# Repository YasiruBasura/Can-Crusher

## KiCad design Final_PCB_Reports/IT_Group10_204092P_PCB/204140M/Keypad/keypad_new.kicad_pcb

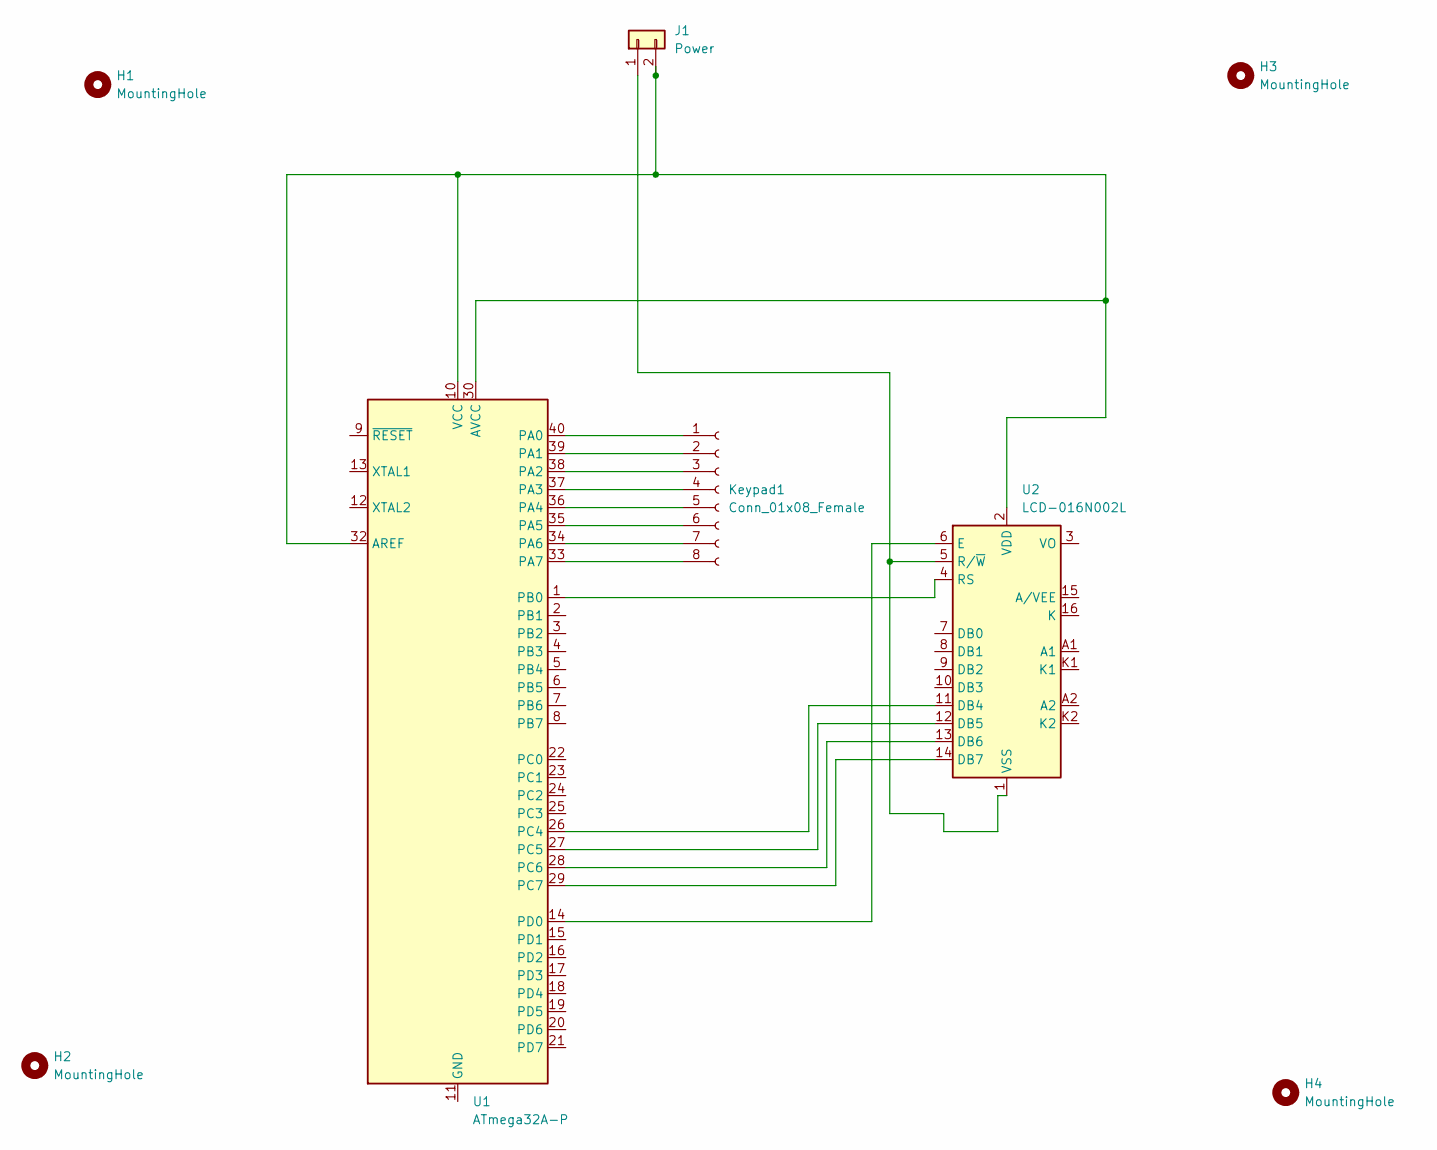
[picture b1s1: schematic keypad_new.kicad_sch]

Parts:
H1, H2, H3, H4: MountingHole; MountingHole_3.5mm_Pad
J1: Power; PinHeader_1x02_P2.54mm_Horizontal
Keypad1: Conn_01x08_Female; PinSocket_1x08_P1.27mm_Vertical
U1: ATmega32A-P; DIP-40_W15.24mm
U2: LCD-016N002L

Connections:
unnamed: Keypad1.1, U1.40 (PA0)
unnamed: Keypad1.2, U1.39 (PA1)
unnamed: Keypad1.3, U1.38 (PA2)
unnamed: Keypad1.4, U1.37 (PA3)
unnamed: Keypad1.5, U1.36 (PA4)
unnamed: Keypad1.6, U1.35 (PA5)
unnamed: Keypad1.7, U1.34 (PA6)
unnamed: Keypad1.8, U1.33 (PA7)
unnamed: U1.1 (PB0), U2.4 (RS)
unnamed: U1.11 (GND), U1.31 (GND)
unnamed: U1.14 (PD0), U2.6 (E)
unnamed: U1.26 (PC4), U2.11 (DB4)
unnamed: U1.27 (PC5), U2.12 (DB5)
unnamed: U1.28 (PC6), U2.13 (DB6)
unnamed: U1.29 (PC7), U2.14 (DB7)
unnamed: J1.2, U1.10 (VCC), U1.30 (AVCC), U1.32 (AREF), U2.2 (VDD)
unnamed: J1.1, U2.1 (VSS), U2.5 (R/~W)

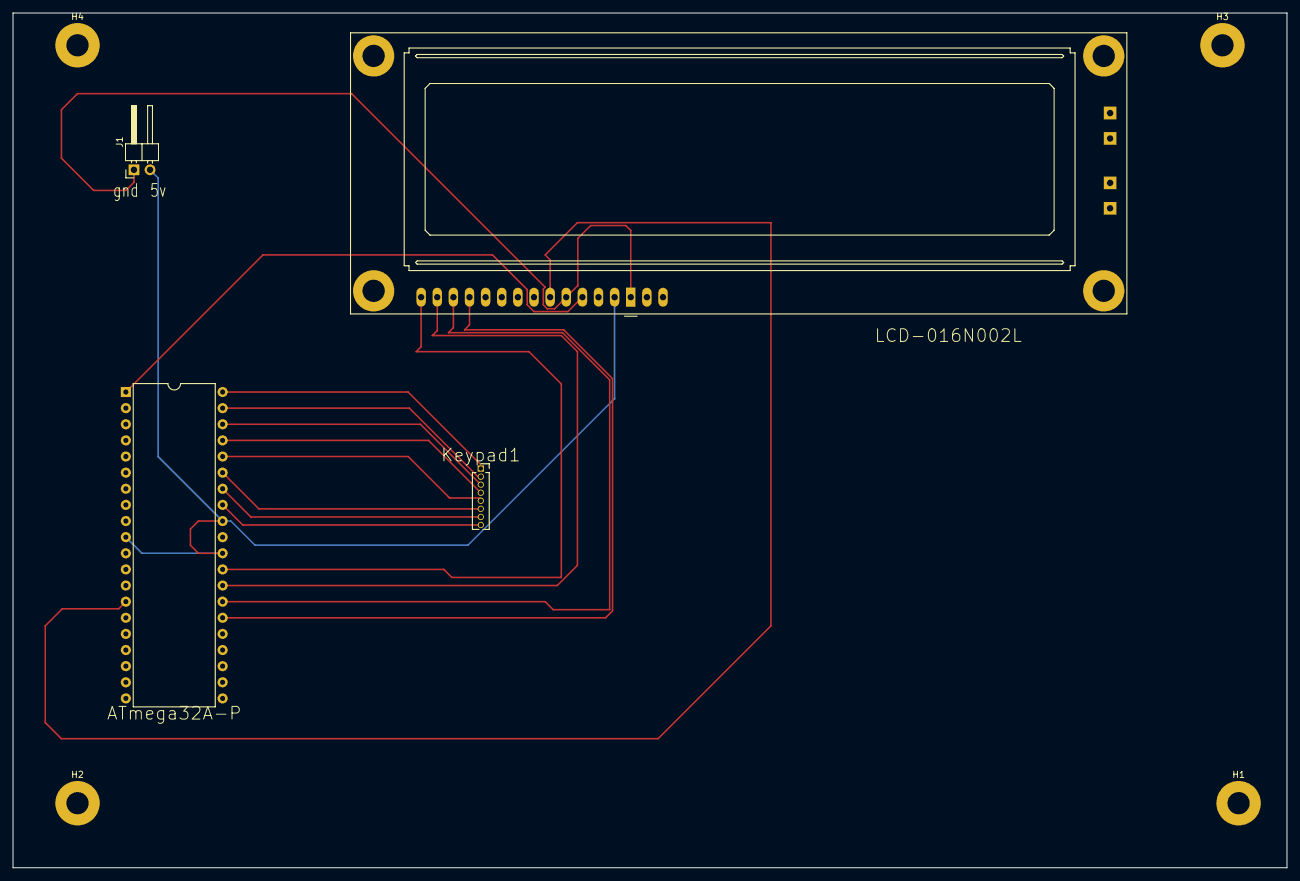
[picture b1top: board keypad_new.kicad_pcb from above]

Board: 2 copper layers, 200.7 x 134.6 mm, 8 parts (0 on the bottom side), 17 nets.

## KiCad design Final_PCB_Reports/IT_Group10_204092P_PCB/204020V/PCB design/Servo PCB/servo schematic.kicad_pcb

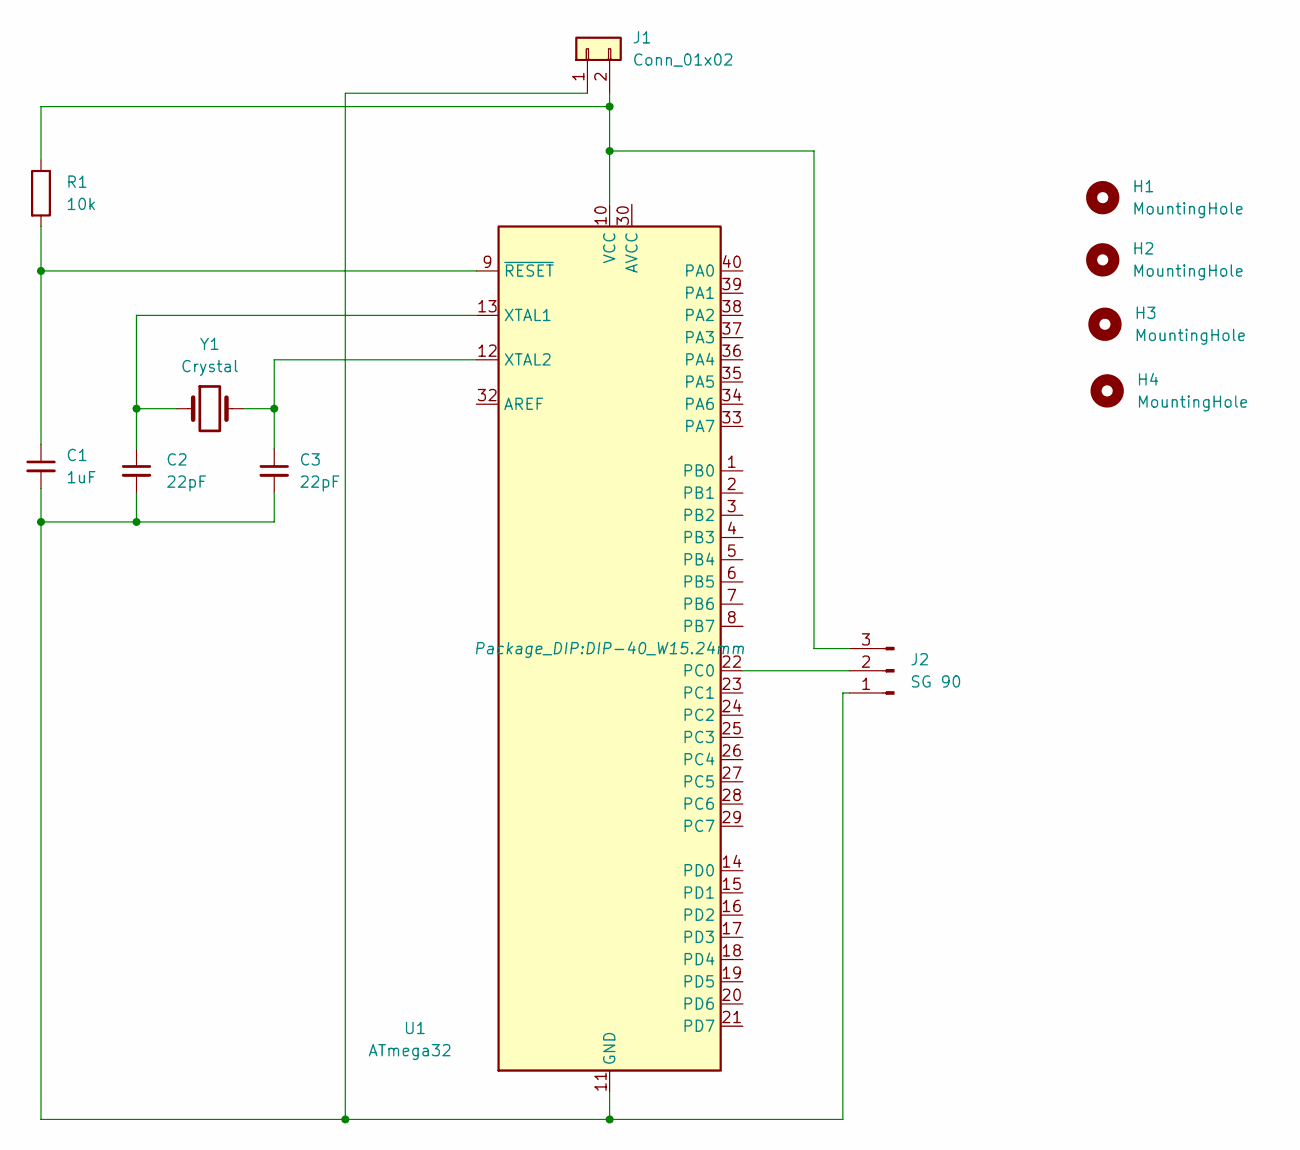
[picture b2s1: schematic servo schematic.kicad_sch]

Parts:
C1: 1uF; CP_Radial_D4.0mm_P1.50mm
C2, C3: 22pF; CP_Radial_D4.0mm_P1.50mm
H1, H2, H3, H4: MountingHole; MountingHole_3.5mm_Pad
J1: Conn_01x02; PinHeader_1x02_P2.54mm_Horizontal
J2: SG 90; PinSocket_1x03_P1.27mm_Vertical
R1: 10k; R_Axial_DIN0204_L3.6mm_D1.6mm_P5.08mm_Horizontal
U1: ATmega32; DIP-40_W15.24mm
Y1: Crystal; Crystal_AT310_D3.0mm_L10.0mm_Vertical

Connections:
unnamed: C1.1, R1.2, U1.9 (~RESET)
unnamed: C1.2, C2.2, C3.2, J1.1, J2.1, U1.11 (GND), U1.31 (GND)
unnamed: C2.1, U1.13 (XTAL1), Y1.1
unnamed: C3.1, U1.12 (XTAL2), Y1.2
unnamed: J1.2, J2.3, R1.1, U1.10 (VCC)
unnamed: J2.2, U1.22 (PC0)

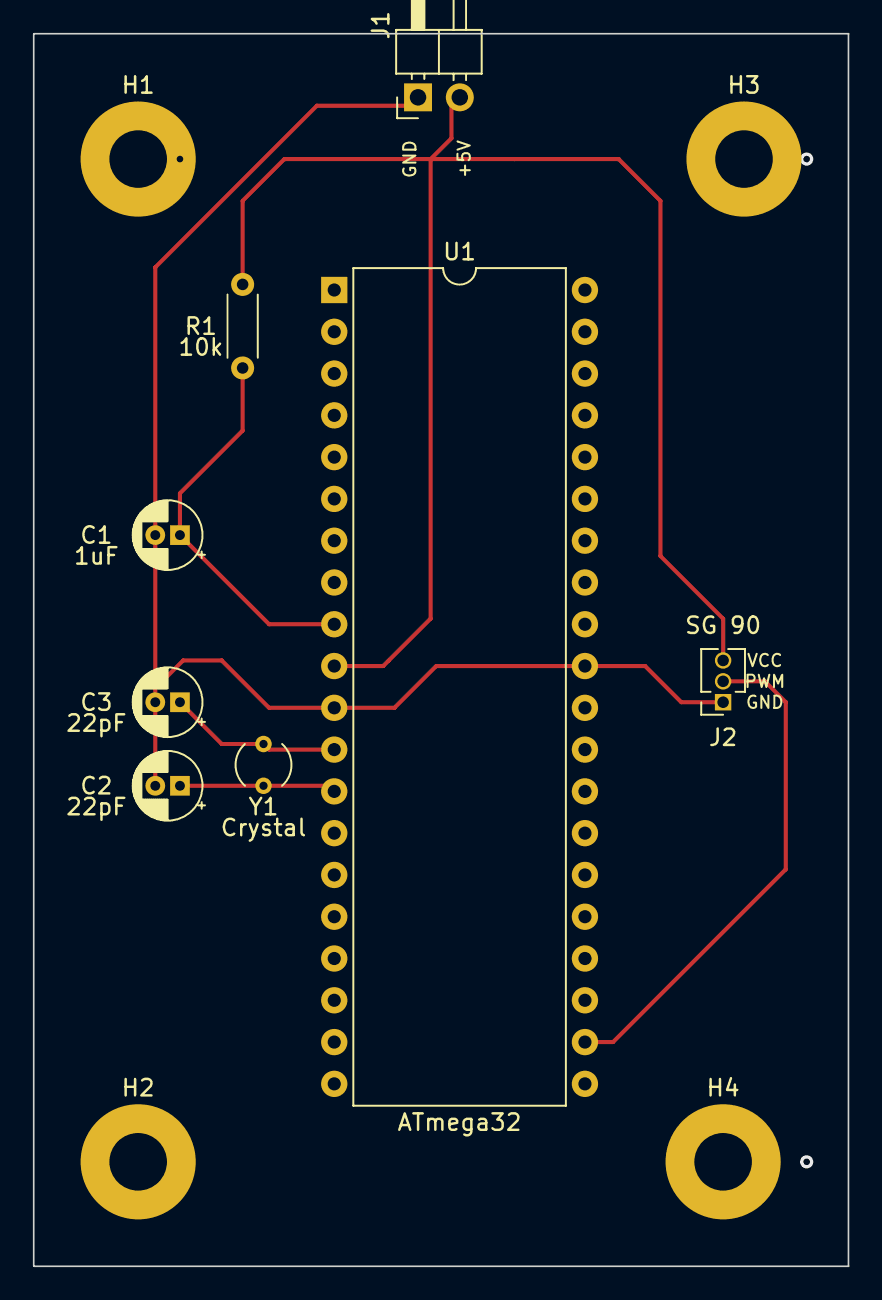
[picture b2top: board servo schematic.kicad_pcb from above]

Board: 2 copper layers, 49.5 x 74.9 mm, 12 parts (0 on the bottom side), 6 nets.

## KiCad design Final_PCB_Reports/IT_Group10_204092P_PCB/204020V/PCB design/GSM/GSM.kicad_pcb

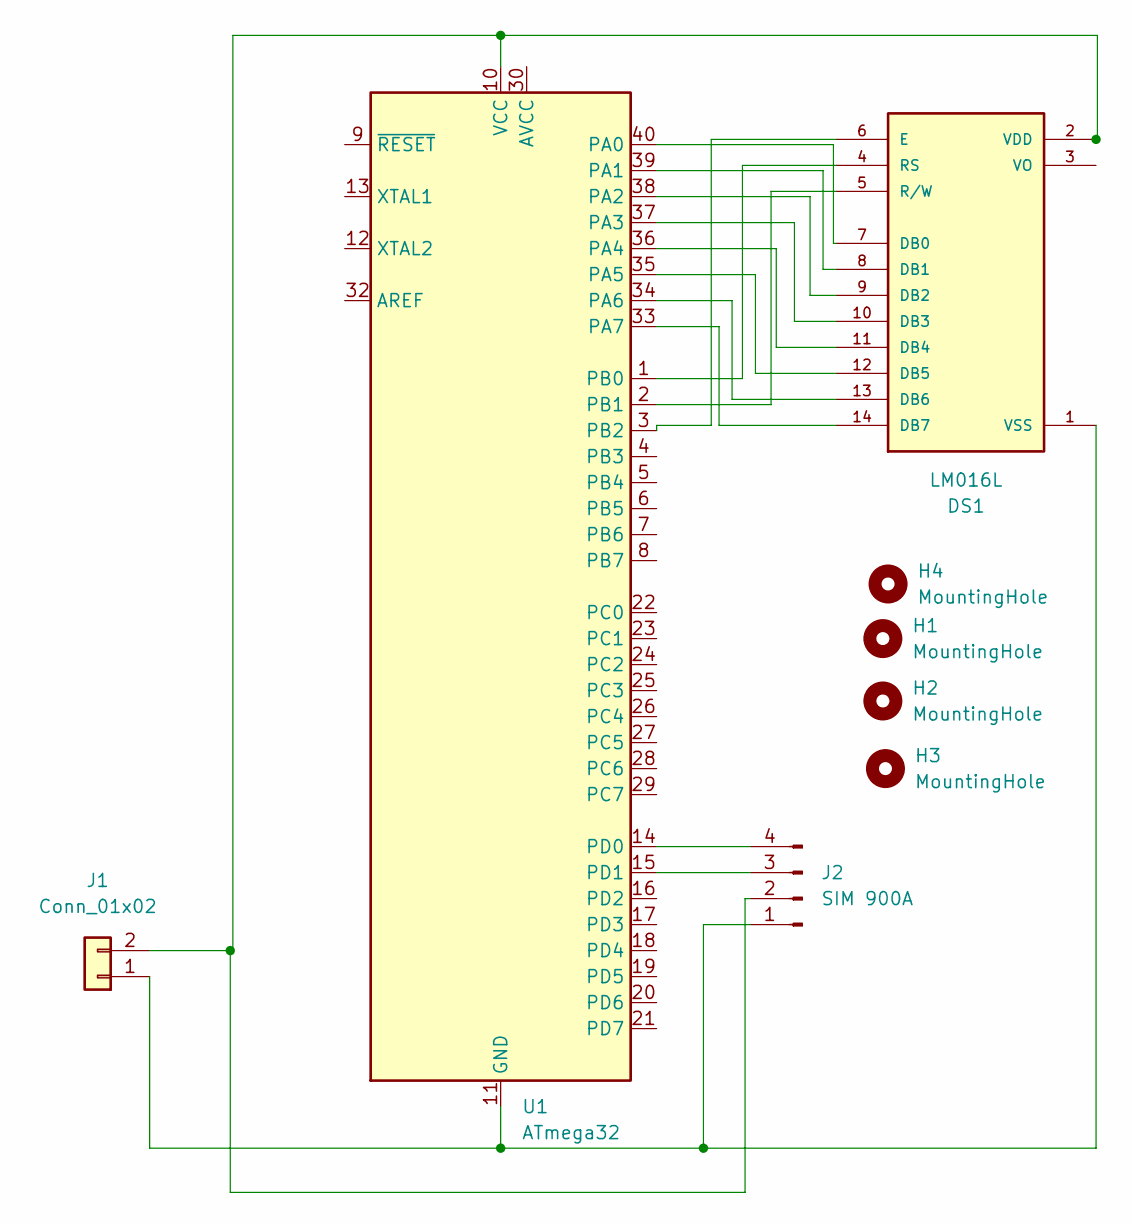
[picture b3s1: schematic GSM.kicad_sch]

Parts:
DS1: LM016L; LCD_LM016L
H1, H2, H3, H4: MountingHole; MountingHole_3.5mm_Pad
J1: Conn_01x02; PinHeader_1x02_P2.54mm_Horizontal
J2: SIM 900A; PinSocket_1x04_P1.27mm_Vertical
U1: ATmega32; DIP-40_W15.24mm

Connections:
unnamed: DS1.4 (RS), U1.1 (PB0)
unnamed: DS1.5 (R/W), U1.2 (PB1)
unnamed: DS1.6 (E), U1.3 (PB2)
unnamed: DS1.7 (DB0), U1.40 (PA0)
unnamed: DS1.8 (DB1), U1.39 (PA1)
unnamed: DS1.9 (DB2), U1.38 (PA2)
unnamed: DS1.10 (DB3), U1.37 (PA3)
unnamed: DS1.11 (DB4), U1.36 (PA4)
unnamed: DS1.12 (DB5), U1.35 (PA5)
unnamed: DS1.13 (DB6), U1.34 (PA6)
unnamed: DS1.14 (DB7), U1.33 (PA7)
unnamed: DS1.1 (VSS), J1.1, J2.1, U1.11 (GND), U1.31 (GND)
unnamed: DS1.2 (VDD), J1.2, J2.2, U1.10 (VCC)
unnamed: J2.3, U1.15 (PD1)
unnamed: J2.4, U1.14 (PD0)

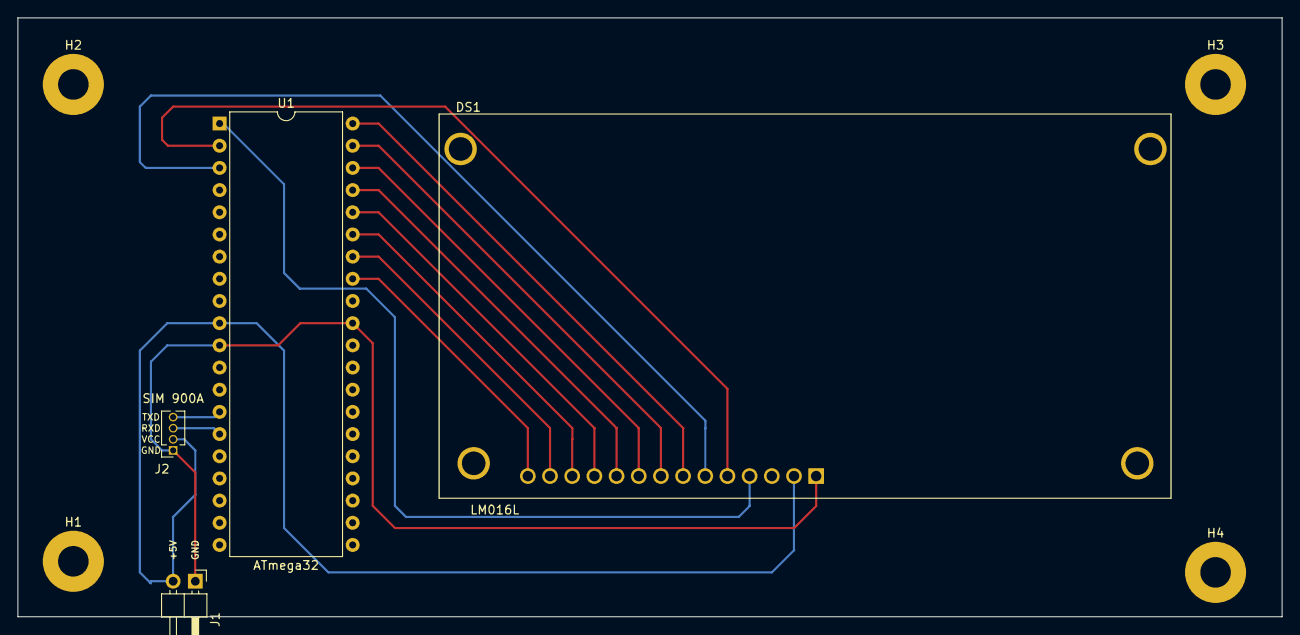
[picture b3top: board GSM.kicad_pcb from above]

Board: 2 copper layers, 144.8 x 68.6 mm, 8 parts (0 on the bottom side), 15 nets.

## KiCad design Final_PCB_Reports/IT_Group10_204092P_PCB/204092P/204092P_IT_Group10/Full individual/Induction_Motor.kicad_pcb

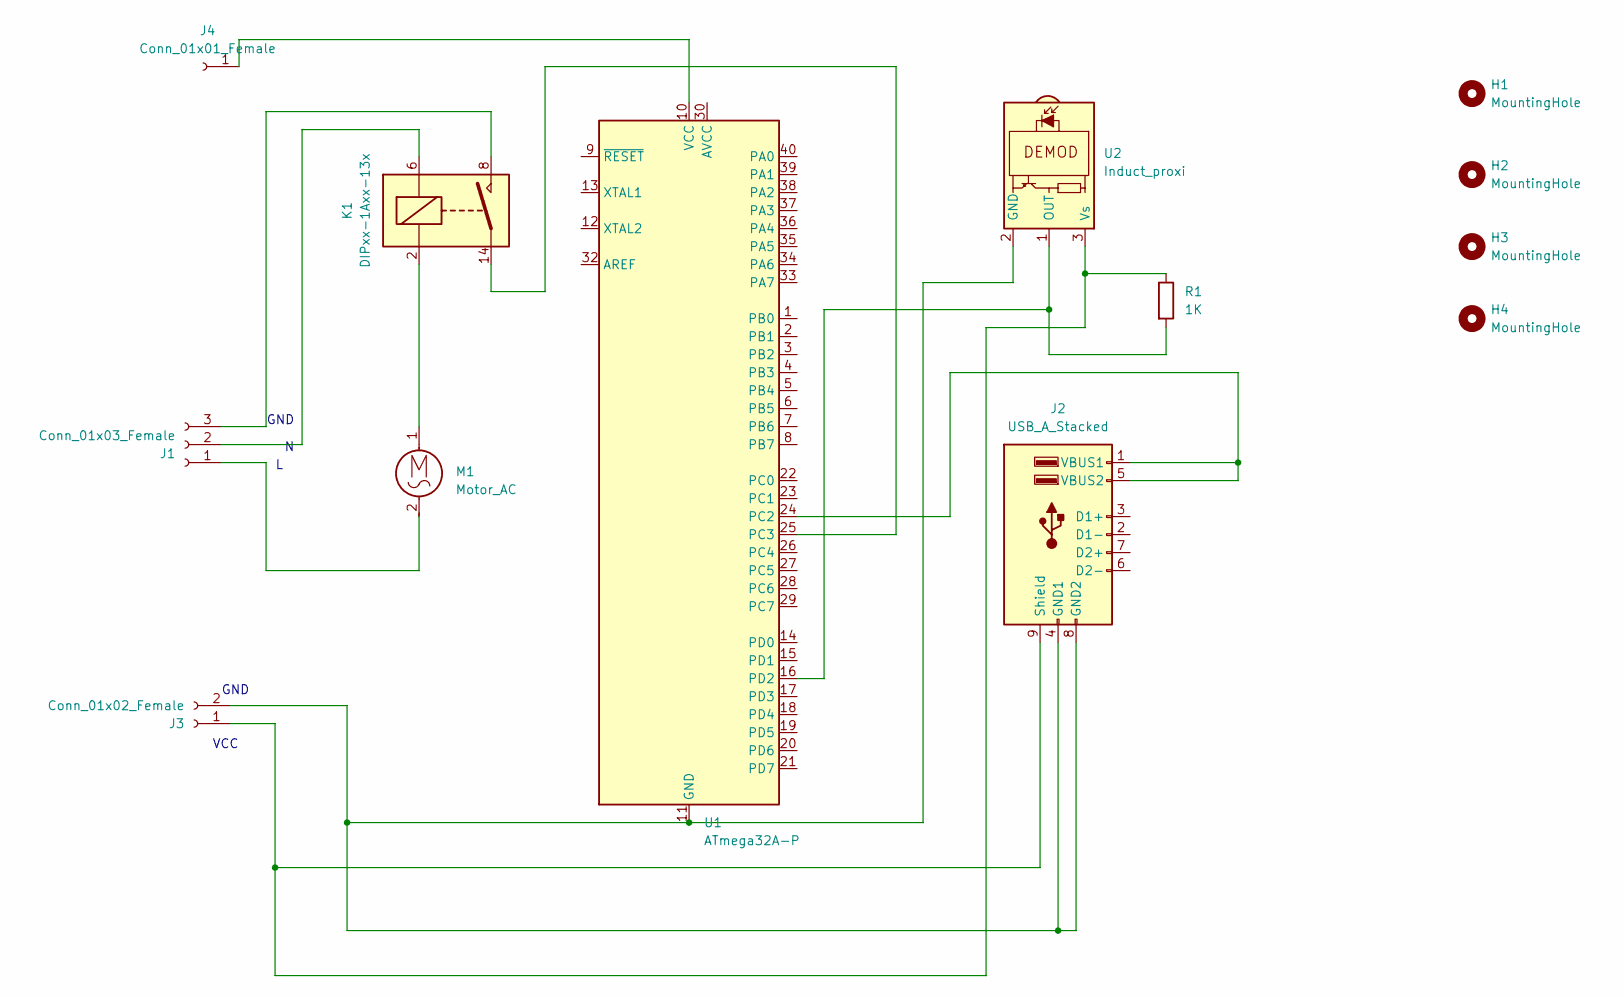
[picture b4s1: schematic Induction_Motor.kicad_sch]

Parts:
H1, H2, H3, H4: MountingHole; MountingHole_3.5mm_Pad
J1: Conn_01x03_Female; PinSocket_1x03_P2.54mm_Vertical
J2: USB_A_Stacked; USB_A_Wuerth_61400826021_Horizontal_Stacked
J3: Conn_01x02_Female; PinSocket_1x02_P2.54mm_Vertical
J4: Conn_01x01_Female; PinSocket_1x01_P2.54mm_Vertical
K1: DIPxx-1Axx-13x; Relay_StandexMeder_DIP_LowProfile
M1: Motor_AC; PinSocket_1x02_P2.54mm_Vertical
R1: 1K; R_Axial_DIN0204_L3.6mm_D1.6mm_P5.08mm_Horizontal
U1: ATmega32A-P; DIP-40_W15.24mm
U2: Induct_proxi; Vishay_MINICAST-3Pin

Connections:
unnamed: J1.1, M1.2
unnamed: J1.2, K1.6
unnamed: J1.3, K1.8
unnamed: J2.1 (VBUS1), J2.5 (VBUS2), U1.24 (PC2)
unnamed: J2.4 (GND1), J2.8 (GND2), J3.2, U1.11 (GND), U1.31 (GND), U2.2 (GND)
unnamed: J2.9 (Shield), J3.1, R1.1, U2.3 (Vs)
unnamed: K1.2, M1.1
unnamed: K1.14, U1.25 (PC3)
unnamed: J4.1, U1.10 (VCC)
unnamed: R1.2, U1.16 (PD2), U2.1 (OUT)

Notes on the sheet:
GND
VCC

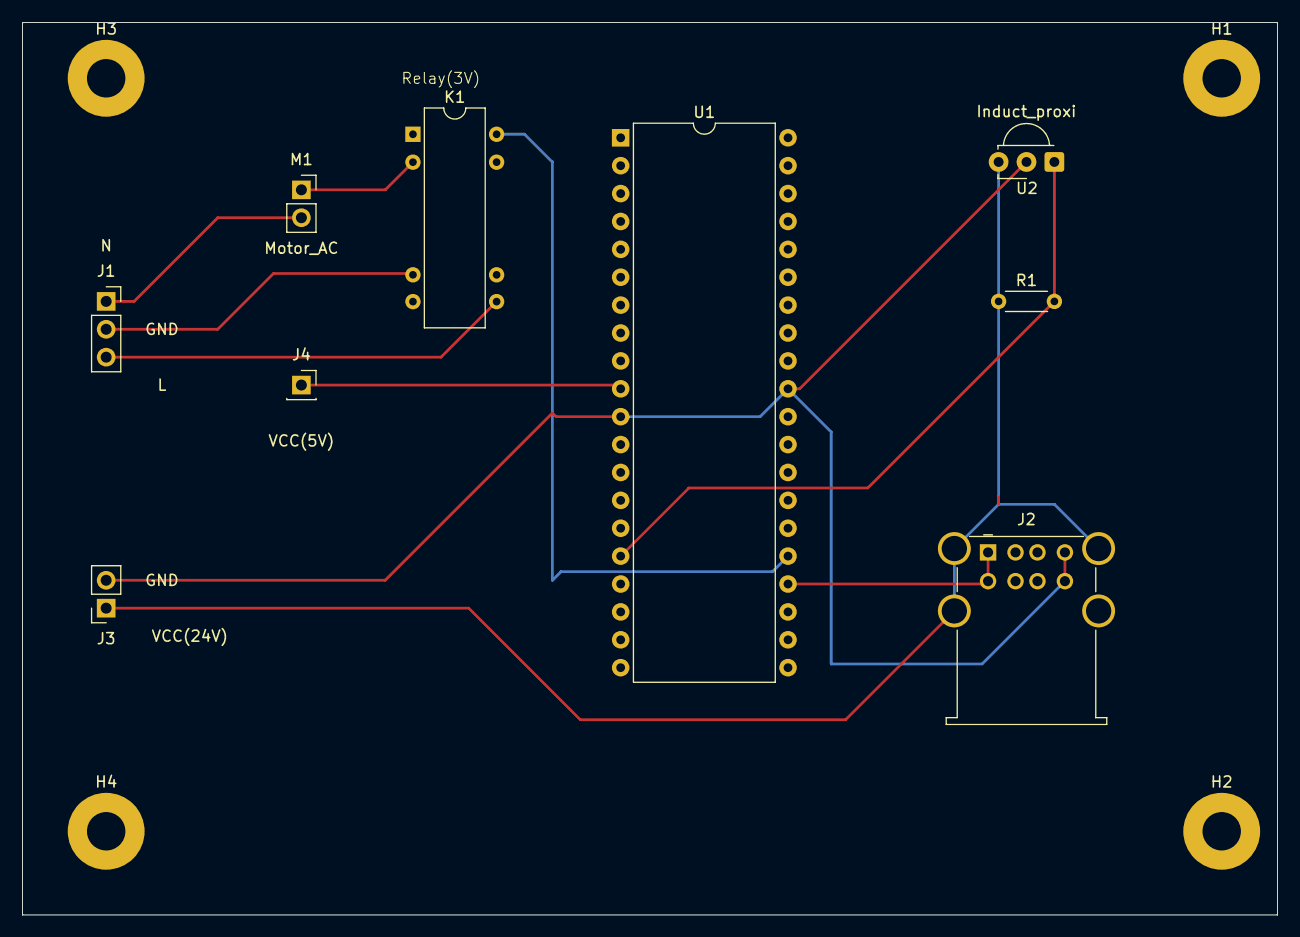
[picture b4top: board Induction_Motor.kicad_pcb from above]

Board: 2 copper layers, 114.3 x 81.3 mm, 13 parts (0 on the bottom side), 10 nets.

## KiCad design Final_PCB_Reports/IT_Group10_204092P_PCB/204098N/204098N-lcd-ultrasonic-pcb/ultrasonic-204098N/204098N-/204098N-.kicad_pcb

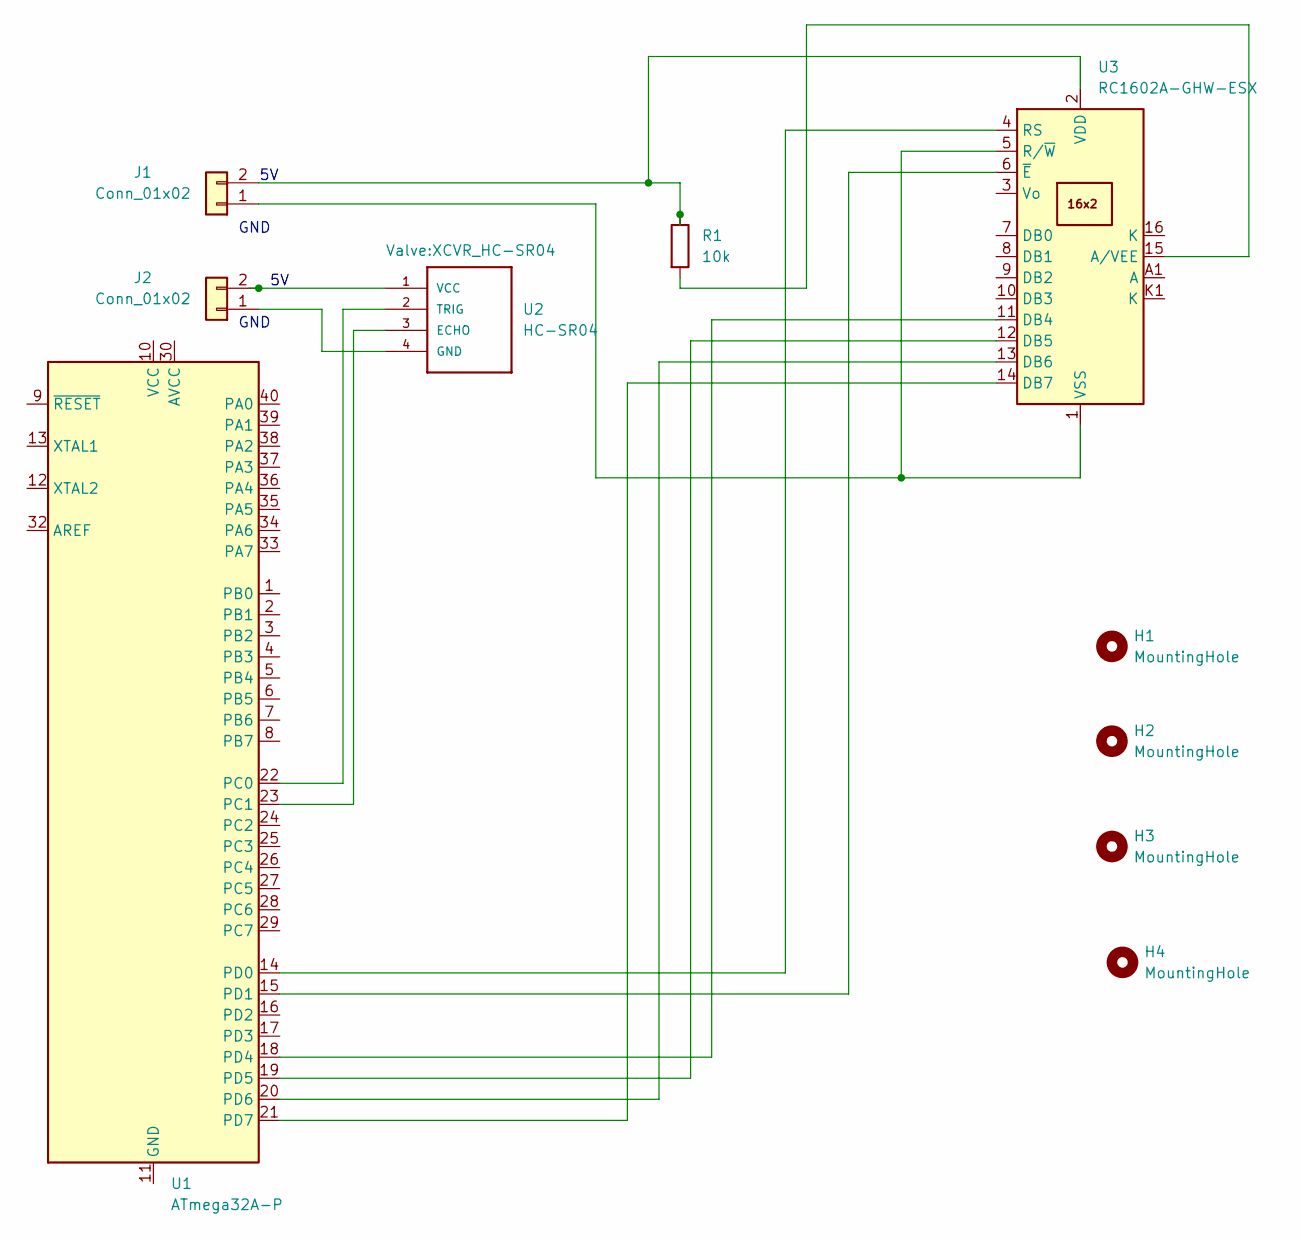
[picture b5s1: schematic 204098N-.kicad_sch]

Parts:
H1, H2, H3, H4: MountingHole; MountingHole_4.5mm
J1, J2: Conn_01x02; PinHeader_1x02_P2.54mm_Horizontal
R1: 10k; R_Axial_DIN0207_L6.3mm_D2.5mm_P15.24mm_Horizontal
U1: ATmega32A-P; DIP-40_W15.24mm
U2: HC-SR04; XCVR_HC-SR04
U3: RC1602A-GHW-ESX; RC1602A

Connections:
unnamed: J1.1, U3.1 (VSS), U3.5 (R/~W)
unnamed: J1.2, R1.1, U3.2 (VDD)
unnamed: R1.2, U3.15 (A/VEE)
unnamed: U1.11 (GND), U1.31 (GND)
unnamed: U1.14 (PD0), U3.4 (RS)
unnamed: U1.15 (PD1), U3.6 (~E)
unnamed: U1.18 (PD4), U3.11 (DB4)
unnamed: U1.19 (PD5), U3.12 (DB5)
unnamed: U1.20 (PD6), U3.13 (DB6)
unnamed: U1.21 (PD7), U3.14 (DB7)
unnamed: U1.22 (PC0), U2.2 (TRIG)
unnamed: U1.23 (PC1), U2.3 (ECHO)
unnamed: J2.2, U2.1 (VCC)
unnamed: J2.1, U2.4 (GND)

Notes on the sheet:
GND

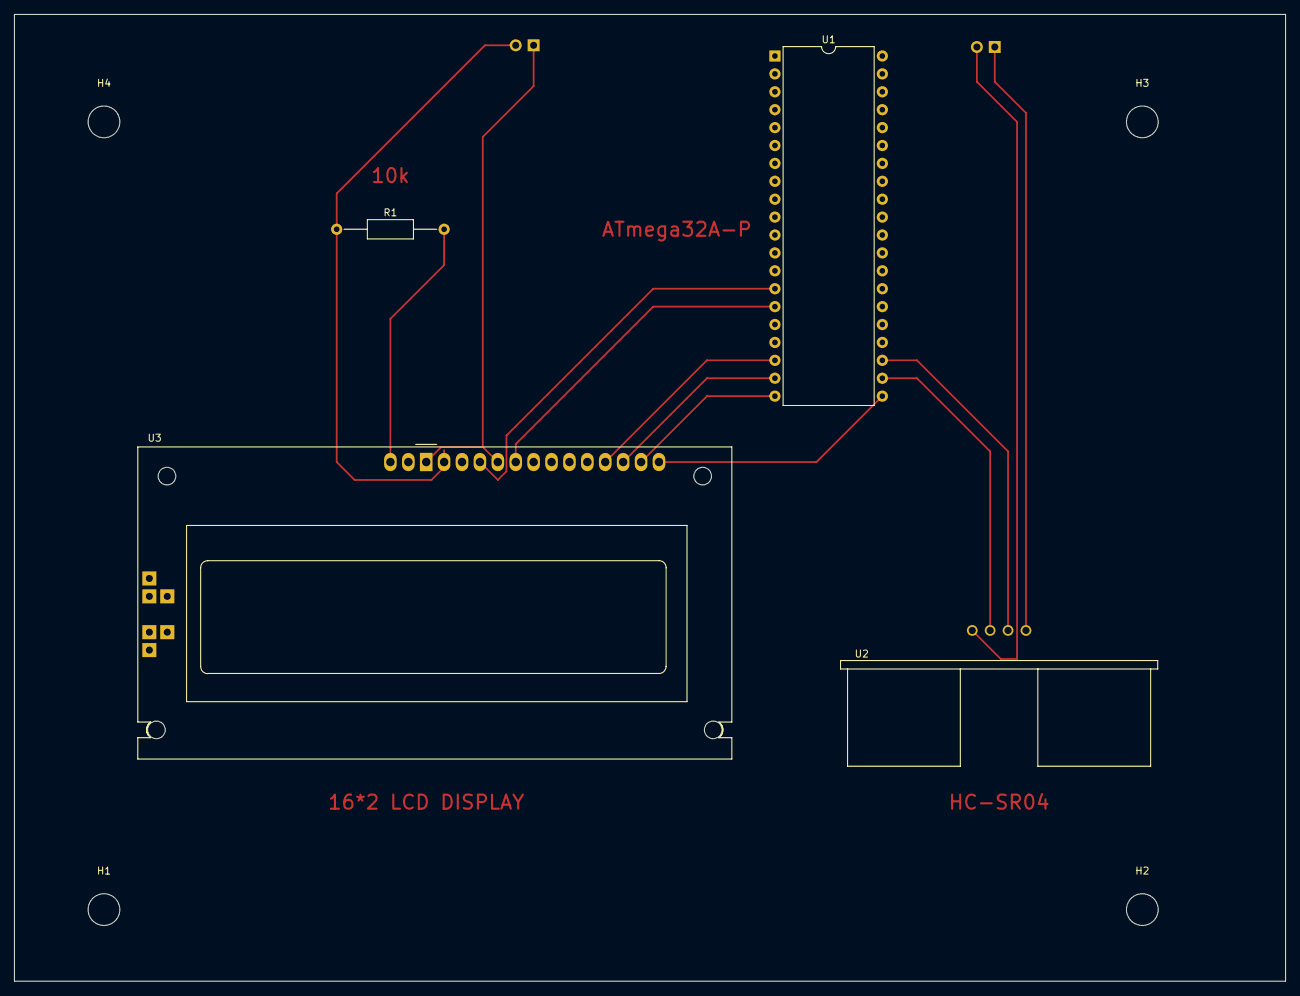
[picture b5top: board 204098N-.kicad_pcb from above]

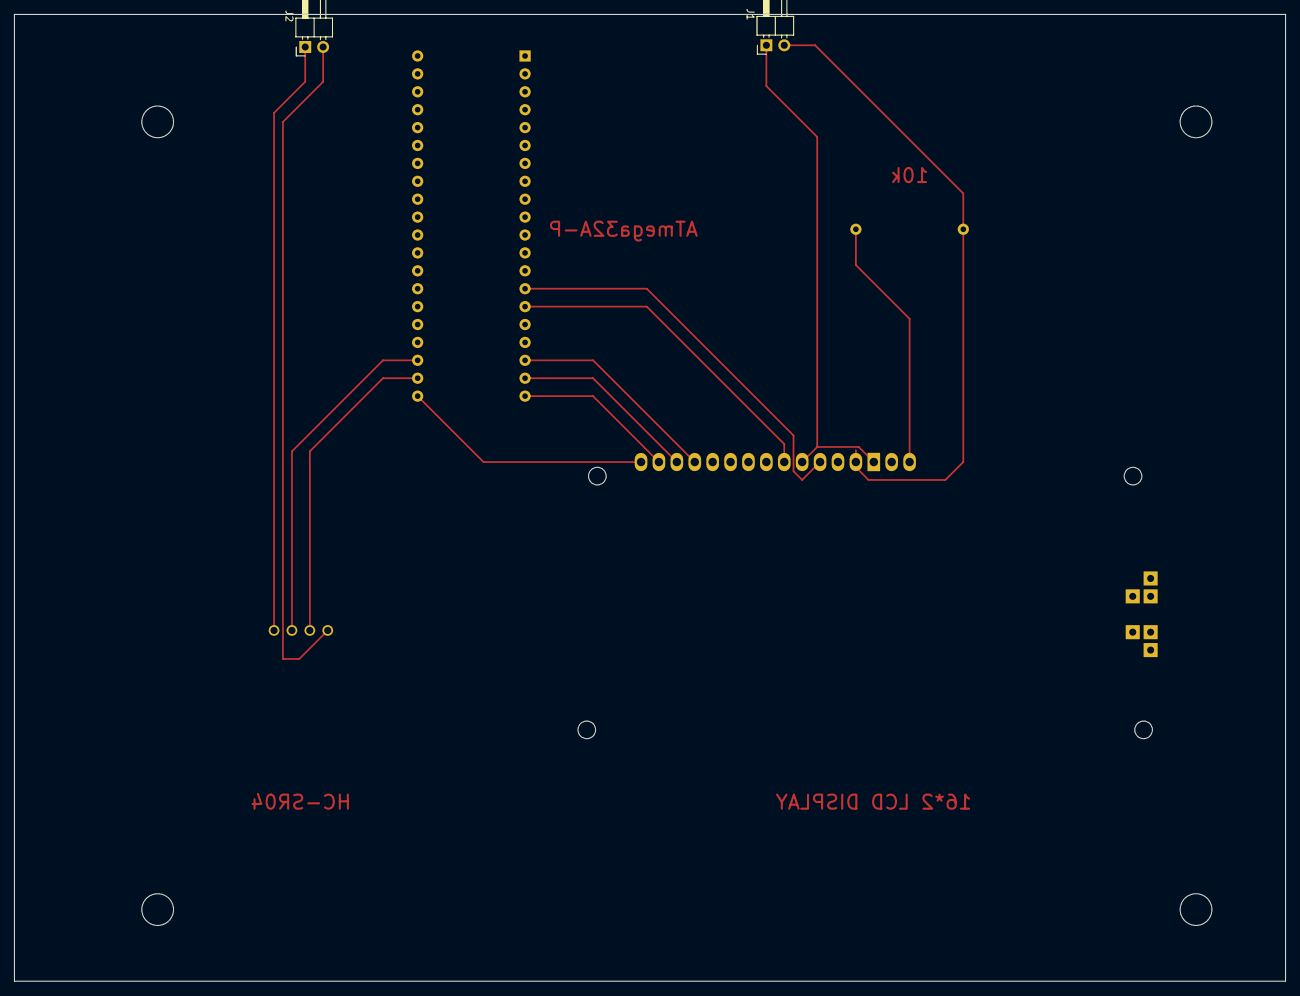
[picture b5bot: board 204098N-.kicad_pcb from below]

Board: 2 copper layers, 180.3 x 137.2 mm, 10 parts (2 on the bottom side), 14 nets.

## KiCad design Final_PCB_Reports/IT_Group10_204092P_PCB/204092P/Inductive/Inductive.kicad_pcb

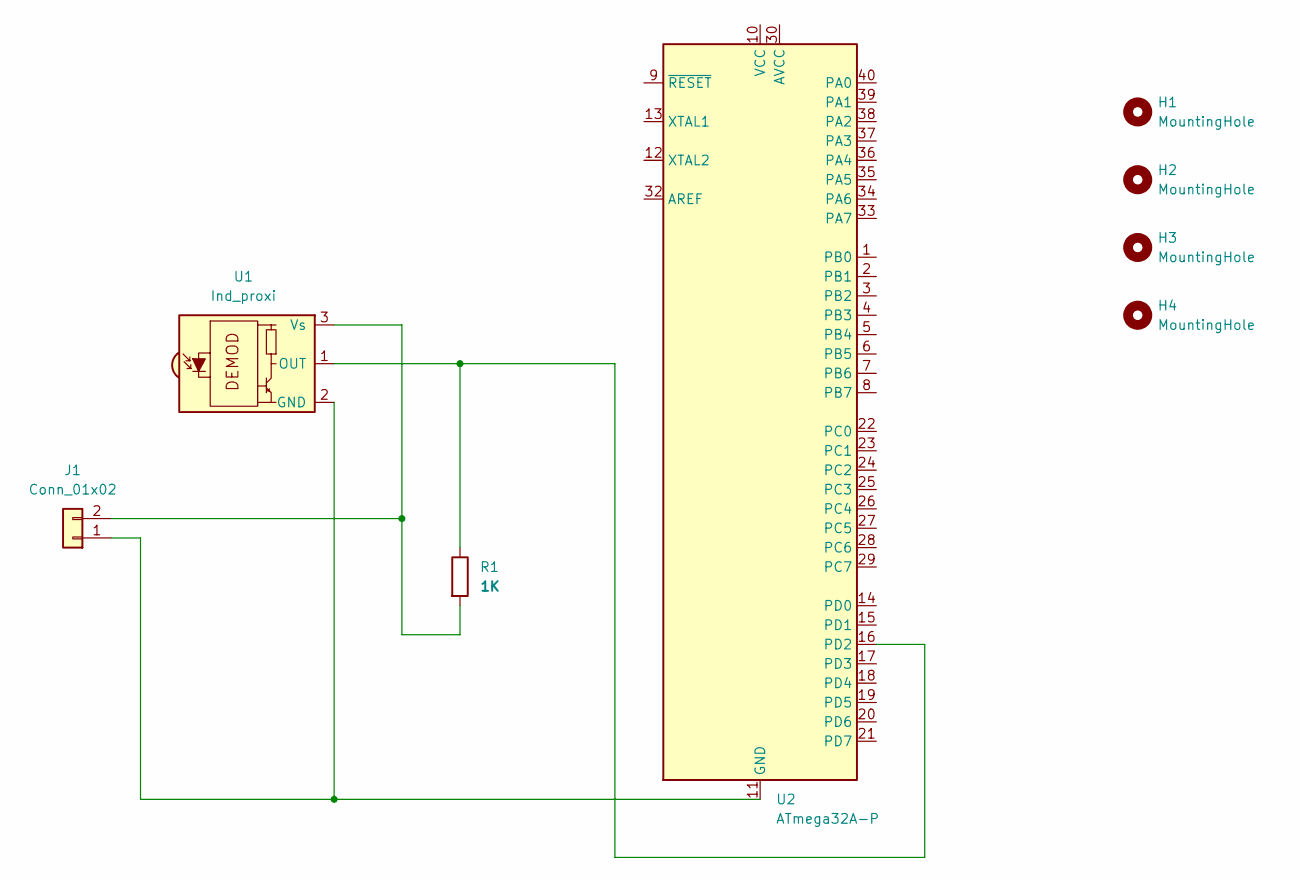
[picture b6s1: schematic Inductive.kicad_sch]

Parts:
H1, H2, H3, H4: MountingHole; MountingHole_3.5mm_Pad
J1: Conn_01x02; PinHeader_1x02_P2.54mm_Horizontal
R1: 1K; R_Axial_DIN0204_L3.6mm_D1.6mm_P5.08mm_Horizontal
U1: Ind_proxi; Vishay_MINICAST-3Pin
U2: ATmega32A-P; DIP-40_W15.24mm

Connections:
unnamed: J1.1, U1.2 (GND), U2.11 (GND), U2.31 (GND)
unnamed: J1.2, R1.2, U1.3 (Vs)
unnamed: R1.1, U1.1 (OUT), U2.16 (PD2)

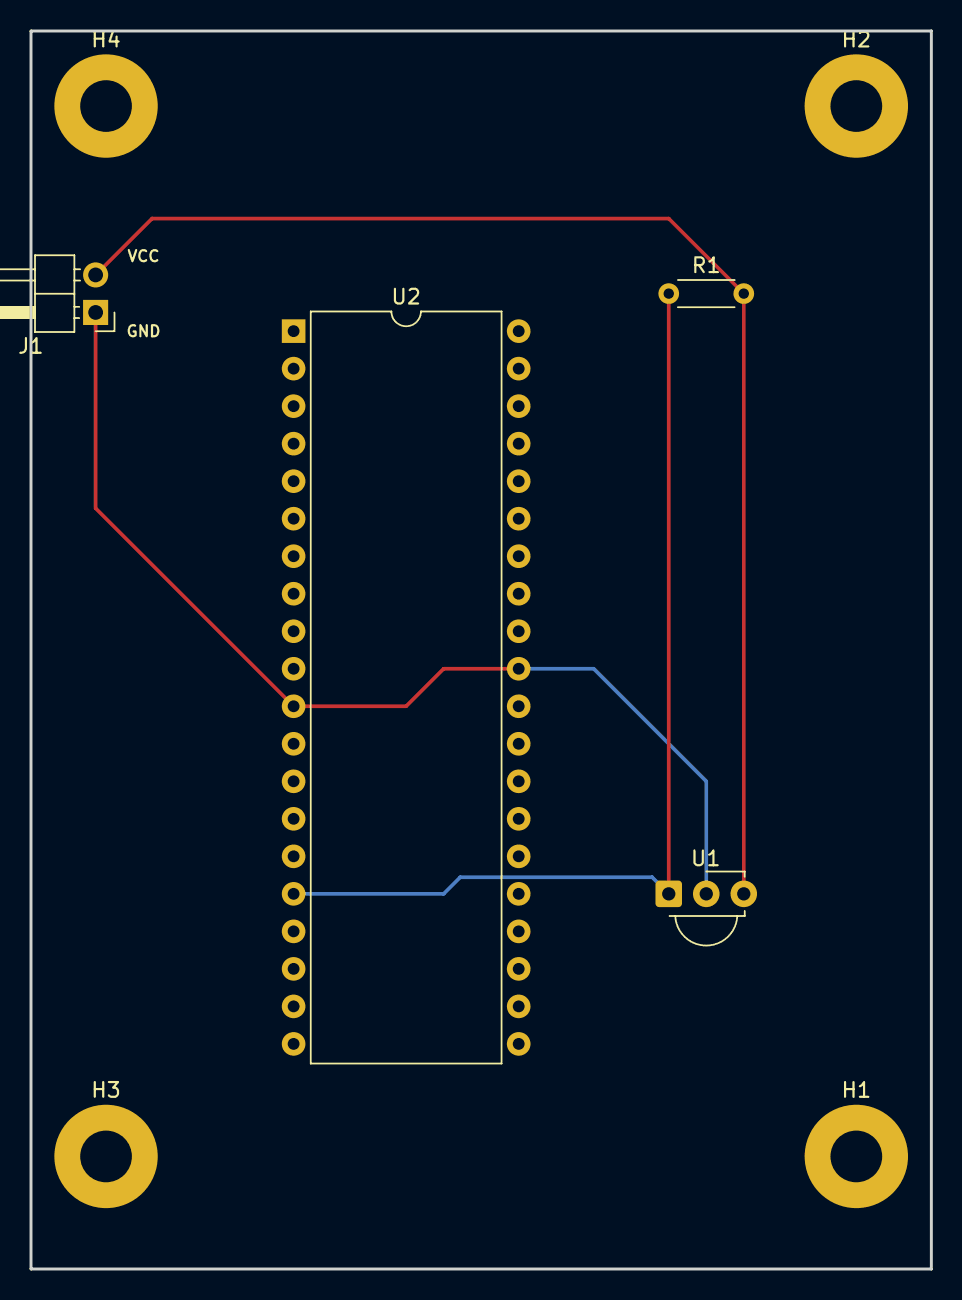
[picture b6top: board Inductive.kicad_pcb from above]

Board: 2 copper layers, 61.0 x 83.8 mm, 8 parts (0 on the bottom side), 3 nets.
